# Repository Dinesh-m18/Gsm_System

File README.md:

View this project on [CADLAB.io](https://cadlab.io/project/29161). 

# Gsm_System

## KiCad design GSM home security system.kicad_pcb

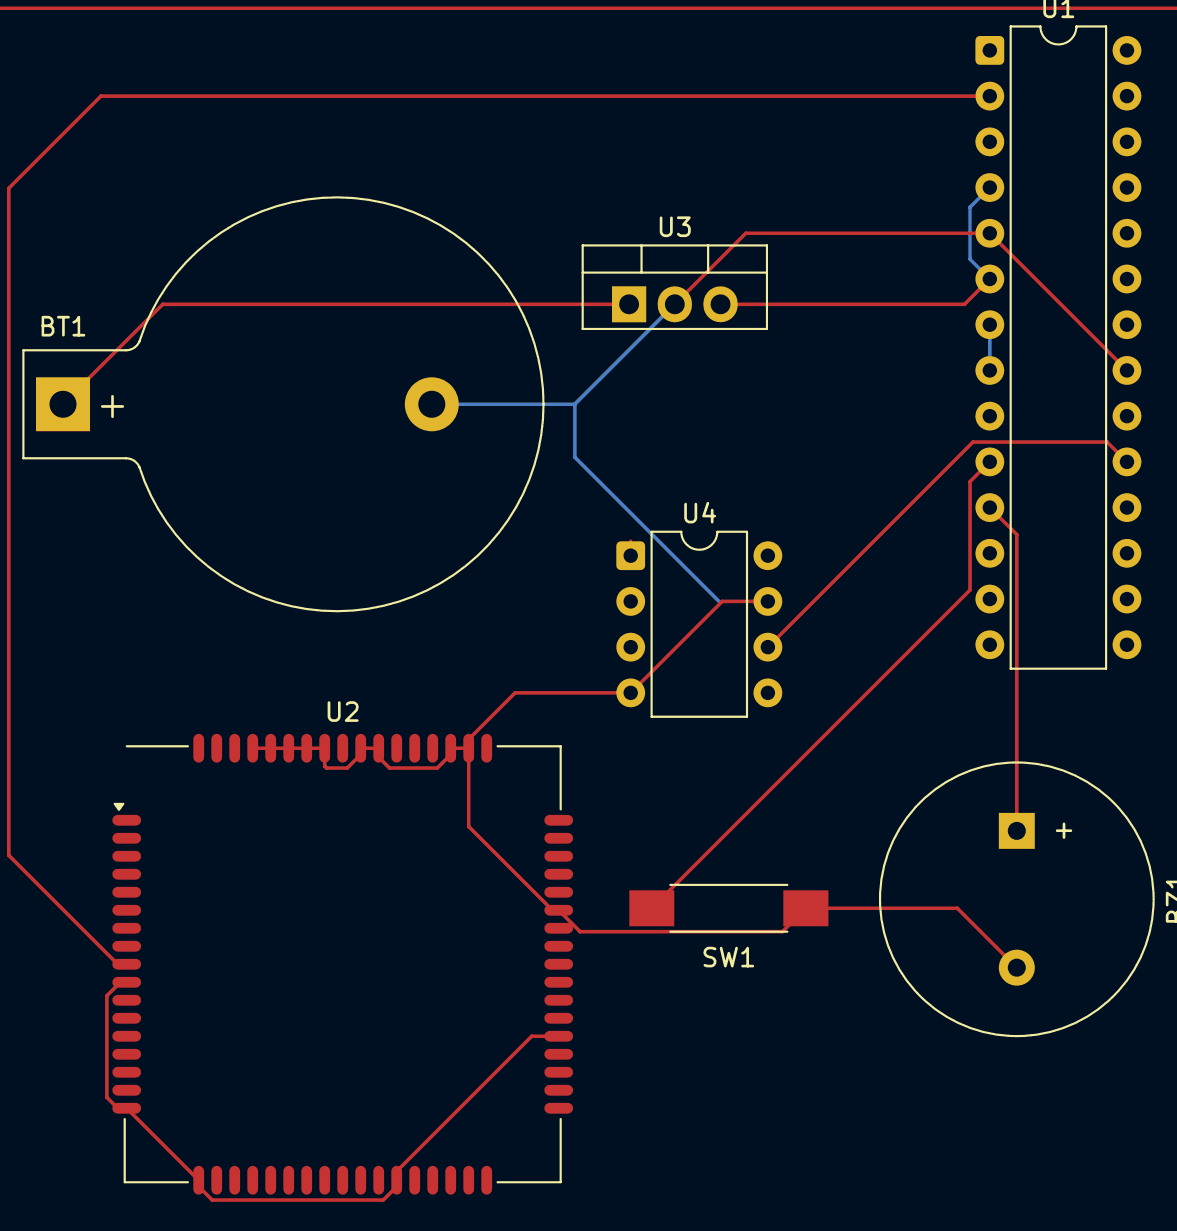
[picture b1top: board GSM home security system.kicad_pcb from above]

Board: 2 copper layers, 7 parts (0 on the bottom side), 8 nets.

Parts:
BT1: Battery; BatteryHolder_Keystone_103_1x20mm
BZ1: Buzzer; Buzzer_15x7.5RM7.6
SW1: SW_Reed; SW_SPST_REED_CT05-XXXX-G1
U1: ATmega328P-A; DIP-28_W7.62mm
U2: SIM900; SIMCom_SIM900
U3: LM7805_TO220; TO-220-3_Vertical
U4: MAX9814; DIP-8_W7.62mm

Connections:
/Crystal Oscillator: U1.7 (XTAL1/PB6), U1.8 (XTAL2/PB7)
GND: BT1.2 (-), BZ1.2 (-), SW1.2, U1.3 (GND), U1.5 (GND), U1.21 (GND), U2.10 (RXD), U2.17 (GND), U2.18 (GND), U2.29 (GND), U2.39 (GND), U2.45 (GND), U2.46 (GND), U2.53 (GND), U2.54 (GND), U2.58 (GND), U2.59 (GND), U2.61 (GND), U2.62 (GND), U2.63 (GND), U2.64 (GND), U2.65 (GND), U3.2 (GND), U4.4 (GND), U4.7 (GND)
unnamed: BT1.1 (+), U3.1 (VI)
unnamed: BZ1.1 (+), U1.11 (PD7)
unnamed: U1.19 (ADC6), U4.6 (MICOUT)
unnamed: U1.2 (PD4), U2.9 (TXD)
unnamed: SW1.1, U1.10 (PD6)
VCC: U1.4 (VCC), U1.6 (VCC), U3.3 (VO)

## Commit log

2025-04-03 Pcb_design
2025-04-03 Backlink to CADLAB.io has been added.
